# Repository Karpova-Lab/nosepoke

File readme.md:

# Nosepoke

Full Documentation here: [https://karpova-lab.github.io/nosepoke/](https://karpova-lab.github.io/nosepoke/)

Ask questions here: [https://github.com/Karpova-Lab/nosepoke/discussions](https://github.com/Karpova-Lab/nosepoke/discussions)

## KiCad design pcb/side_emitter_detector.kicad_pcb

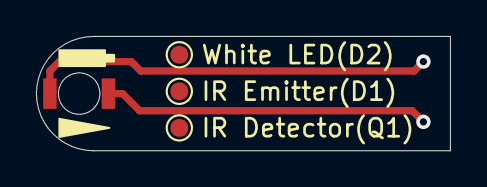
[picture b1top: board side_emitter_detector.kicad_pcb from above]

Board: 2 copper layers, 23.0 x 6.4 mm, 5 parts (1 on the bottom side), 2 nets.

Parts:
D1: LED; 1206_reverse_smd
IR Detector(Q1): TestPoint; TestPoint_Pad_D1.0mm
IR Emitter(D1): TestPoint; TestPoint_Pad_D1.0mm
J1: Conn_01x02_Male; board_to_board_joint
White LED(D2): TestPoint; TestPoint_Pad_D1.0mm

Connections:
unnamed: D1.1, J1.2
unnamed: D1.2, J1.1

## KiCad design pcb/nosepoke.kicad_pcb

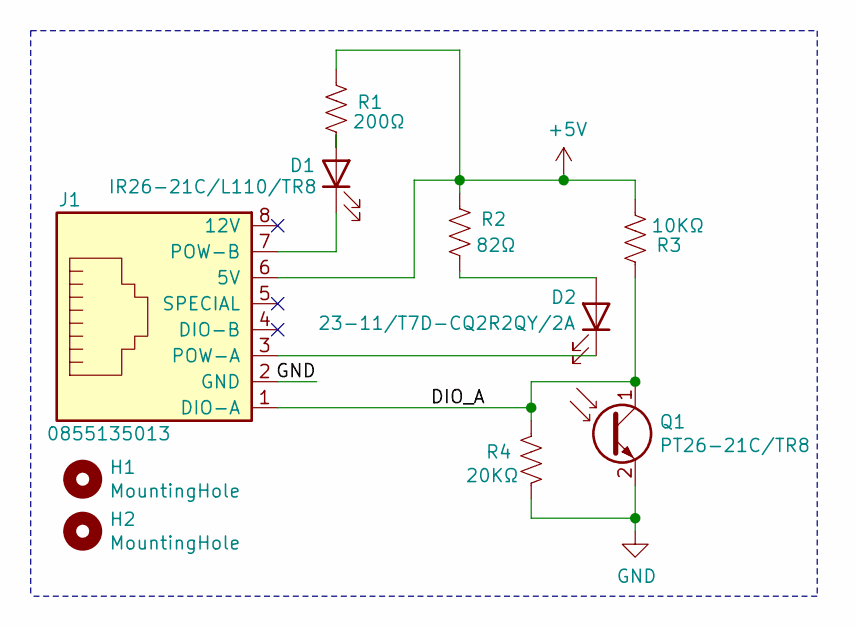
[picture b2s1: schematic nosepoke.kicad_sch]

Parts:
D1: IR26-21C/L110/TR8; board_to_board_joint
D2: 23-11/T7D-CQ2R2QY/2A; board_to_board_joint
H1, H2: MountingHole; MountingHole_2.7mm_M2.5
J1: 0855135013; RJ45_SMD_Vertical
Q1: PT26-21C/TR8; board_to_board_joint
R1: 200Ω; R_0603_1608Metric
R2: 82Ω; R_0603_1608Metric
R3: 10KΩ; R_0603_1608Metric
R4: 20KΩ; R_0603_1608Metric

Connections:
+5V: J1.6 (5V), R1.2, R2.2, R3.2
/DIO_A: J1.1 (DIO-A), Q1.1 (C), R3.1, R4.2
GND: J1.2 (GND), Q1.2 (E), R4.1
unnamed: D1.1 (K), J1.7 (POW-B)
unnamed: D1.2 (A), R1.1
unnamed: D2.1 (K), J1.3 (POW-A)
unnamed: D2.2 (A), R2.1

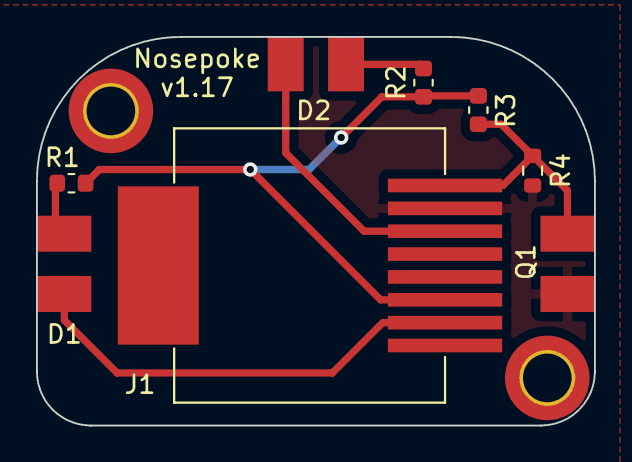
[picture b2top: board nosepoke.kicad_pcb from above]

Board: 2 copper layers, 31.0 x 21.6 mm, 10 parts (0 on the bottom side), 7 nets.

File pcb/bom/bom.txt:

"Qty","Reference","Description","Value/MPN","Purchase Link"
"1","D1","IR LED","IR26-21C/L110/TR8","https://www.digikey.com/products/en?keywords=1080-1357-1-ND"
"1","D2","Diffused White LED","23-11/T7D-CQ2R2QY/2A","https://www.digikey.com/products/en?keywords=1080-1593-1-ND"
"1","J1","RJ45 Jack","0855135013","https://www.digikey.com/products/en?keywords=WM3553CT-ND"
"1","Q1","Phototransistor","PT26-21C/TR8","https://www.digikey.com/products/en?keywords=1080-1386-1-ND"
"1","R1","0603 Resistor","200Ω","https://www.digikey.com/products/en?keywords=P330HCT-ND"
"1","R2","0603 Resistor","82Ω","https://www.digikey.com/products/en?keywords=311-82.0HRCT-ND"
"1","R3","0603 Resistor","10KΩ","https://www.digikey.com/product-detail/en/RC0603JR-0710KL/31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"
"1","R4","0603 Resistor","20KΩ","https://www.digikey.com/product-detail/en/RC0603JR-0710KL/31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"

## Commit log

2019-01-04 fixed broken CAD file links
2019-01-17 Doc update
2019-03-28 Documentation update
2019-12-11 Added readme with new licenses
2020-01-13 preparing to add kicad project
2020-04-13 Update to pyControl compatible nosepoke. Plastic body is shorter. No longer have lick detection. New shorter PCBs, designed in KiCAD. Big documentation update.
2020-04-13 readme update
2020-04-14 temp delete
2020-04-14 image link fix
2020-04-14 fix doc pcb images
2020-04-27 Improved assembly instructions with pictures.
2020-04-27 fixed missing picture
2020-06-17 fixed broken ibom link
2021-03-17 rear pcb v1.16
2021-06-03 transition to hugo
2021-06-03 added nosepoke aligner
2021-06-08 css updates
2021-06-10 images are can now be clicked to enlarge
2021-06-11 doc theme updates
2021-06-22 pictures added to doc overview
2021-06-22 fixed broken image links
2021-06-22 rearranged docs. added BOM and design files section
2021-06-22 fixed broken assembly image links
2022-10-13 backside PCB v1.17
2022-10-13 doc updates for PCB v1.17
2023-01-12 updated hugo theme submodule
2023-01-12 R1 link in docs now points to a 200Ω resistor on digikey
    fixes https://github.com/Karpova-Lab/nosepoke/issues/2
2023-07-18 fixed broken image link
2023-08-28 updated example task
